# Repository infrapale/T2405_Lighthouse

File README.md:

# T2405_Lighthouse
Collection of Lighthouse software

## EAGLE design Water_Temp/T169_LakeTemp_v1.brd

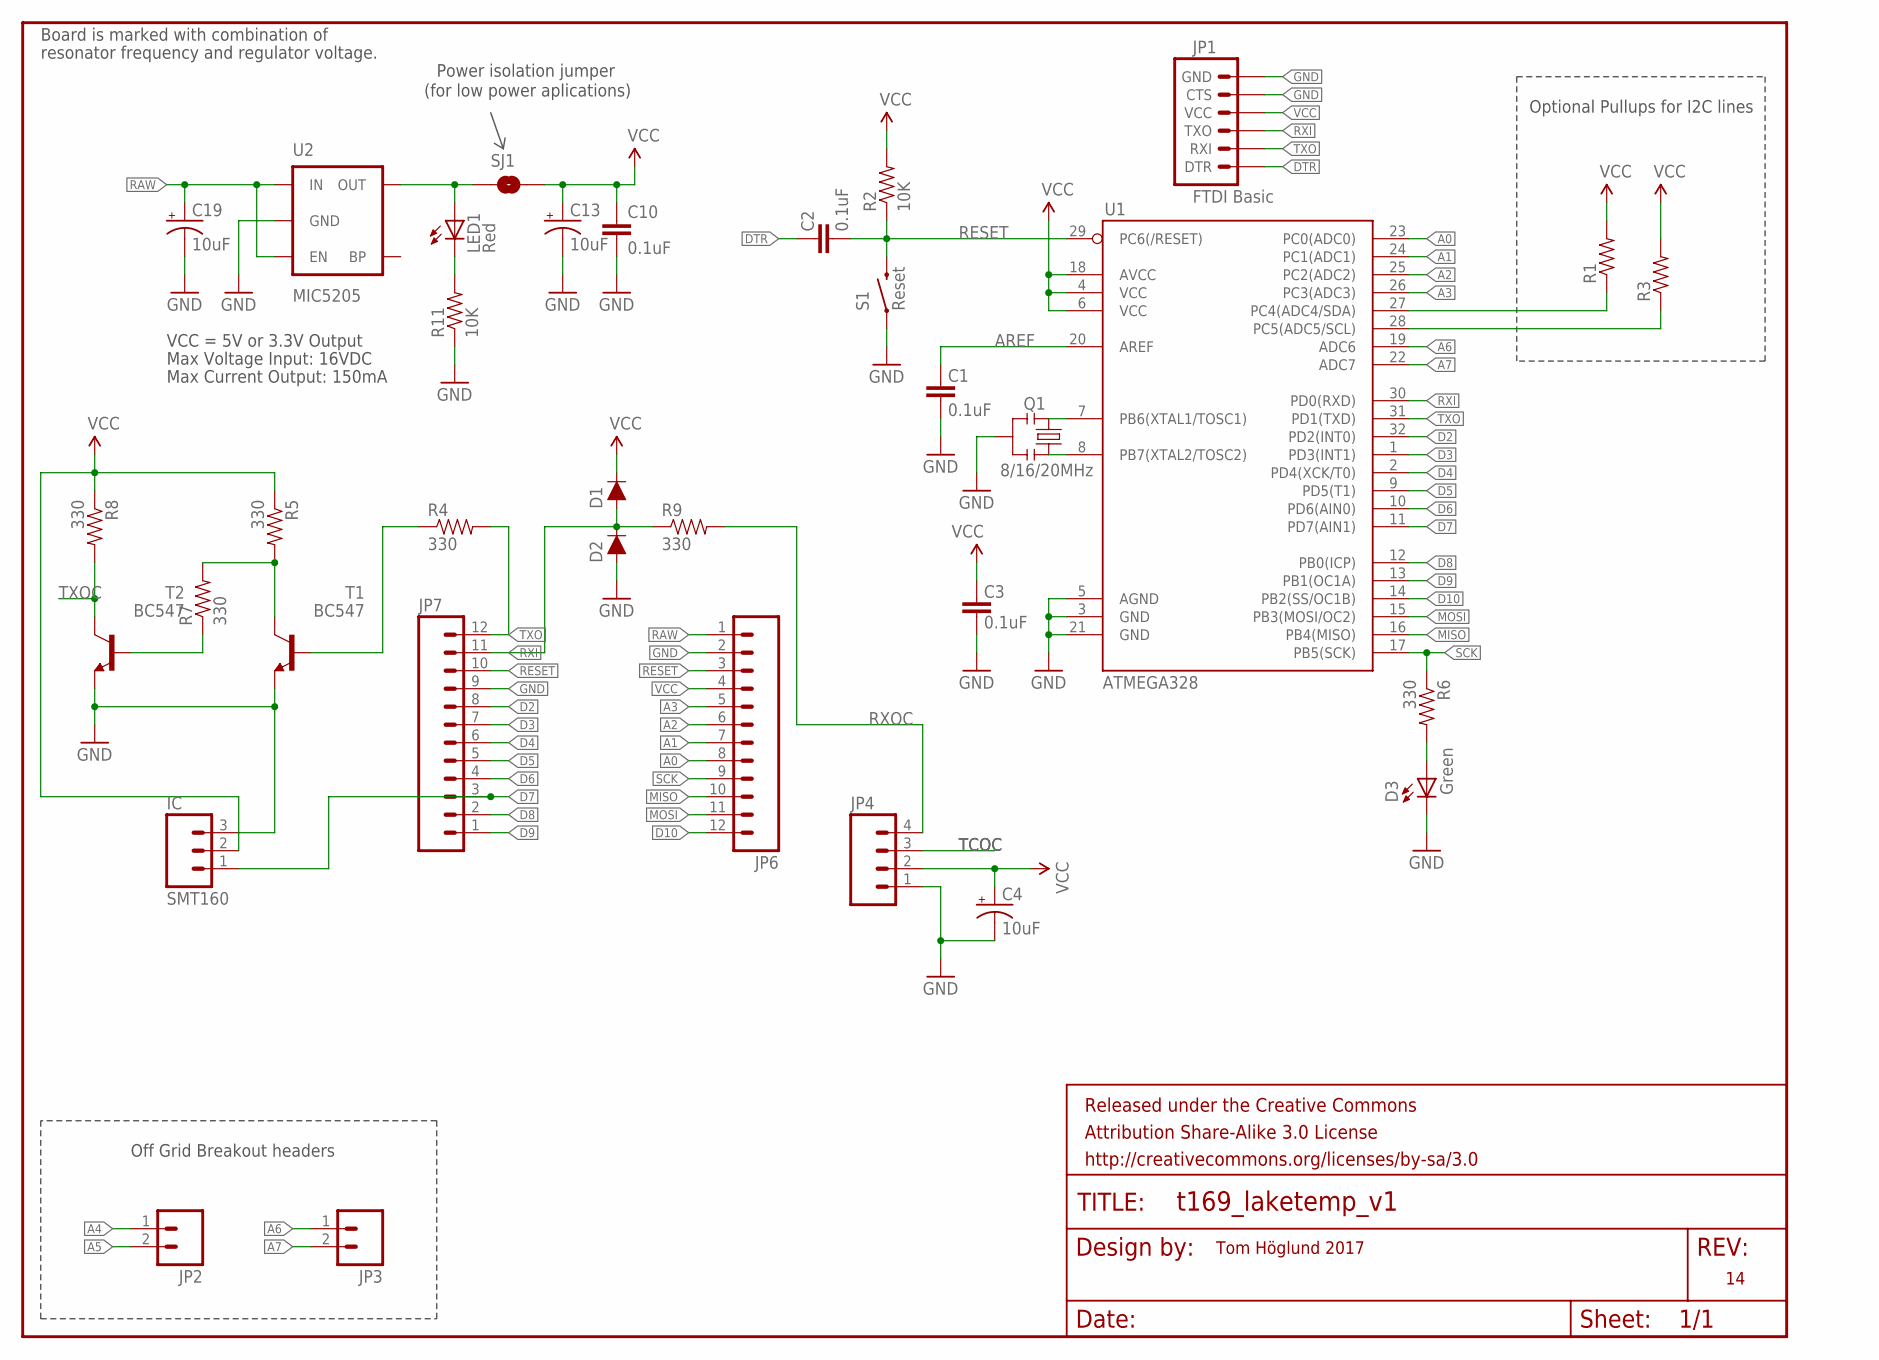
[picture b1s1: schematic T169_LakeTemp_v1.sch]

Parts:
C1, C2, C3, C10: 0.1uF; 0603-CAP
C4, C13, C19: 10uF; EIA3216
D1, D2: DIODE-1N4148
D3: Green; 0603-LED-ALT1
FRAME1: FRAME-LETTER; CREATIVE_COMMONS
IC: SMT160; 1X03
JP1: FTDI Basic; 1X06
JP2, JP3: M02PTH; 1X02
JP4: M04PTH; 1X04
JP6, JP7: M12PTH; 1X12
LED1: Red; 0603-LED-ALT1
Q1: 8/16/20MHz; RESONATOR-SMD-1:1
R1, R3: RESISTOR0603-RES; 0603-RES
R2, R11: 10K; 0603-RES
R4, R5, R6, R7, R8, R9: 330; 0603-RES
S1: Reset; TACTILE-SWITCH-SMD-ALT01
SJ1: SOLDERJUMPERNC; SJ_2S
T1, T2: BC547; TO92
U1: ATMEGA328; TQFP32-08
U2: MIC5205; SOT23-5

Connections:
3.3V: C4.A (+), D1.C, IC.2, JP4.2, R5.1, R8.1
A0: JP6.8, U1.23 (PC0(ADC0))
A1: JP6.7, U1.24 (PC1(ADC1))
A2: JP6.6, U1.25 (PC2(ADC2))
A3: JP6.5, U1.26 (PC3(ADC3))
A4: JP2.1, R1.1, U1.27 (PC4(ADC4/SDA))
A5: JP2.2, R3.1, U1.28 (PC5(ADC5/SCL))
A6: JP3.1, U1.19 (ADC6)
A7: JP3.2, U1.22 (ADC7)
AREF: C1.2, U1.20 (AREF)
D2: JP7.8, U1.32 (PD2(INT0))
D3: JP7.7, U1.1 (PD3(INT1))
D4: JP7.6, U1.2 (PD4(XCK/T0))
D5: JP7.5, U1.9 (PD5(T1))
D6: JP7.4, U1.10 (PD6(AIN0))
D7: IC.1, JP7.3, U1.11 (PD7(AIN1))
D8: JP7.2, U1.12 (PB0(ICP))
D9: JP7.1, U1.13 (PB1(OC1A))
D10: JP6.12, U1.14 (PB2(SS/OC1B))
DTR: C2.2, JP1.1 (DTR)
GND: C1.1, C3.1, C4.C (-), C10.2, C13.C (-), C19.C (-), D2.A, D3.C, IC.3, JP1.5 (CTS), JP1.6 (GND), JP4.1, JP6.2, JP7.9, Q1.2, R11.1, S1.1, S1.2 (1), T1.1 (E), T2.1 (E), U1.3 (GND), U1.5 (AGND), U1.21 (GND), U2.2 (GND)
MISO: JP6.10, U1.16 (PB4(MISO))
MOSI: JP6.11, U1.15 (PB3(MOSI/OC2))
unnamed: Q1.3, U1.8 (PB7(XTAL2/TOSC2))
unnamed: Q1.1, U1.7 (PB6(XTAL1/TOSC1))
unnamed: LED1.A, SJ1.1, U2.5 (OUT)
unnamed: LED1.C, R11.2
unnamed: R4.1, T1.2 (B)
unnamed: R5.2, R7.2, T1.3 (C)
unnamed: D3.A, R6.2
unnamed: R7.1, T2.2 (B)
RAW: C19.A (+), JP6.1, U2.1 (IN), U2.3 (EN)
RESET: C2.1, JP6.3, JP7.10, R2.1, S1.3 (2), S1.4 (2), U1.29 (PC6(/RESET))
RXI: D1.A, D2.C, JP1.3 (TXO), JP7.11, R9.1, U1.30 (PD0(RXD))
RXOC: JP4.4, R9.2
SCK: JP6.9, R6.1, U1.17 (PB5(SCK))
TCOC: JP4.3
TXO: JP1.2 (RXI), JP7.12, R4.2, U1.31 (PD1(TXD))
TXOC: R8.2, T2.3 (C)
VCC: C3.2, C10.1, C13.A (+), JP1.4 (VCC), JP6.4, R1.2, R2.2, R3.2, SJ1.2, U1.4 (VCC), U1.6 (VCC), U1.18 (AVCC)

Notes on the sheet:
Tom Höglund 2017
Max Voltage Input: 16VDC
Max Current Output: 150mA
Board is marked with combination of
resonator frequency and regulator voltage.
VCC = 5V or 3.3V Output
Optional Pullups for I2C lines
Off Grid Breakout headers
Power isolation jumper
(for low power aplications)

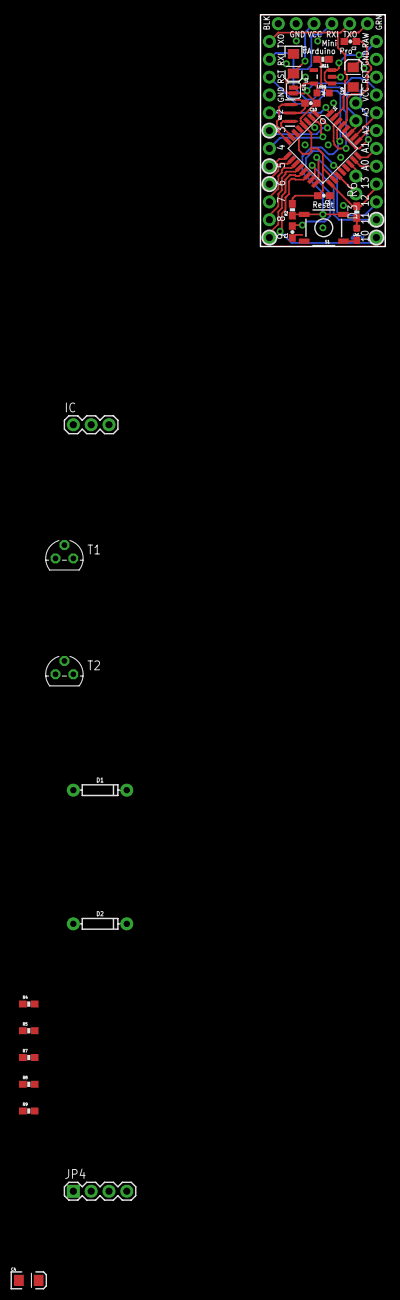
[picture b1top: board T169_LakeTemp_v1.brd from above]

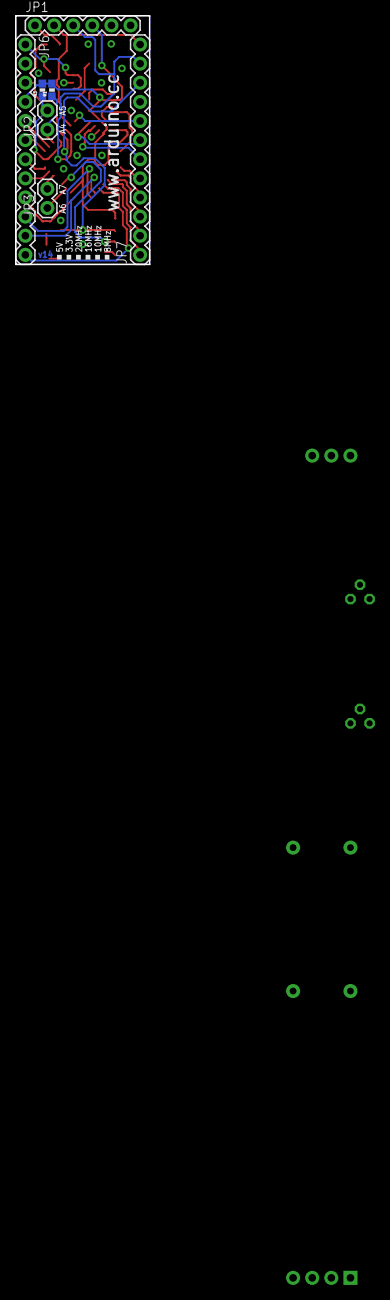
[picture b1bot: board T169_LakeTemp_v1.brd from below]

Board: 2 copper layers, 17.8 x 33.0 mm, 36 parts (7 on the bottom side), 39 nets.

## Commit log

2024-06-04 draft 2024 version
2024-06-06 fixing the main controller
2024-06-09 code cleaned and documented
2024-06-11 code cleanup and fixes
2026-05-27 old SensorCom.ino update

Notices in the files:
parts and their libraries:
SparkFun-Aesthetics: Licensing: CC v3.0 Share-Alike You are welcome to use this library for commercial purposes.
SparkFun-Aesthetics: Released under the Creative Commons Attribution Share-Alike 3.0 License
SparkFun-Aesthetics: http://creativecommons.org/licenses/by-sa/3.0
